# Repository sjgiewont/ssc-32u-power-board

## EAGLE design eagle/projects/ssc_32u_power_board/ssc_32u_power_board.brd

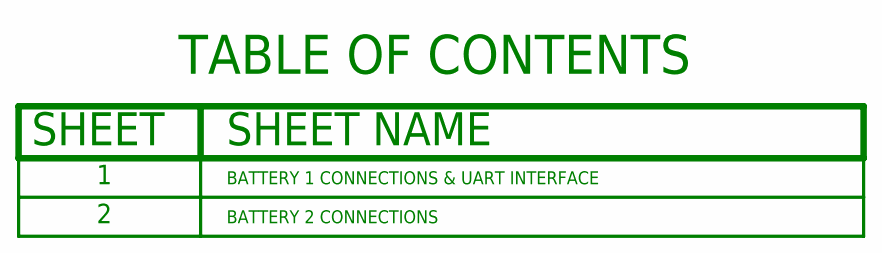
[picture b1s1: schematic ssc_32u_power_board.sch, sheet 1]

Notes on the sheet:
BATTERY 1 CONNECTIONS & UART INTERFACE
BATTERY 2 CONNECTIONS

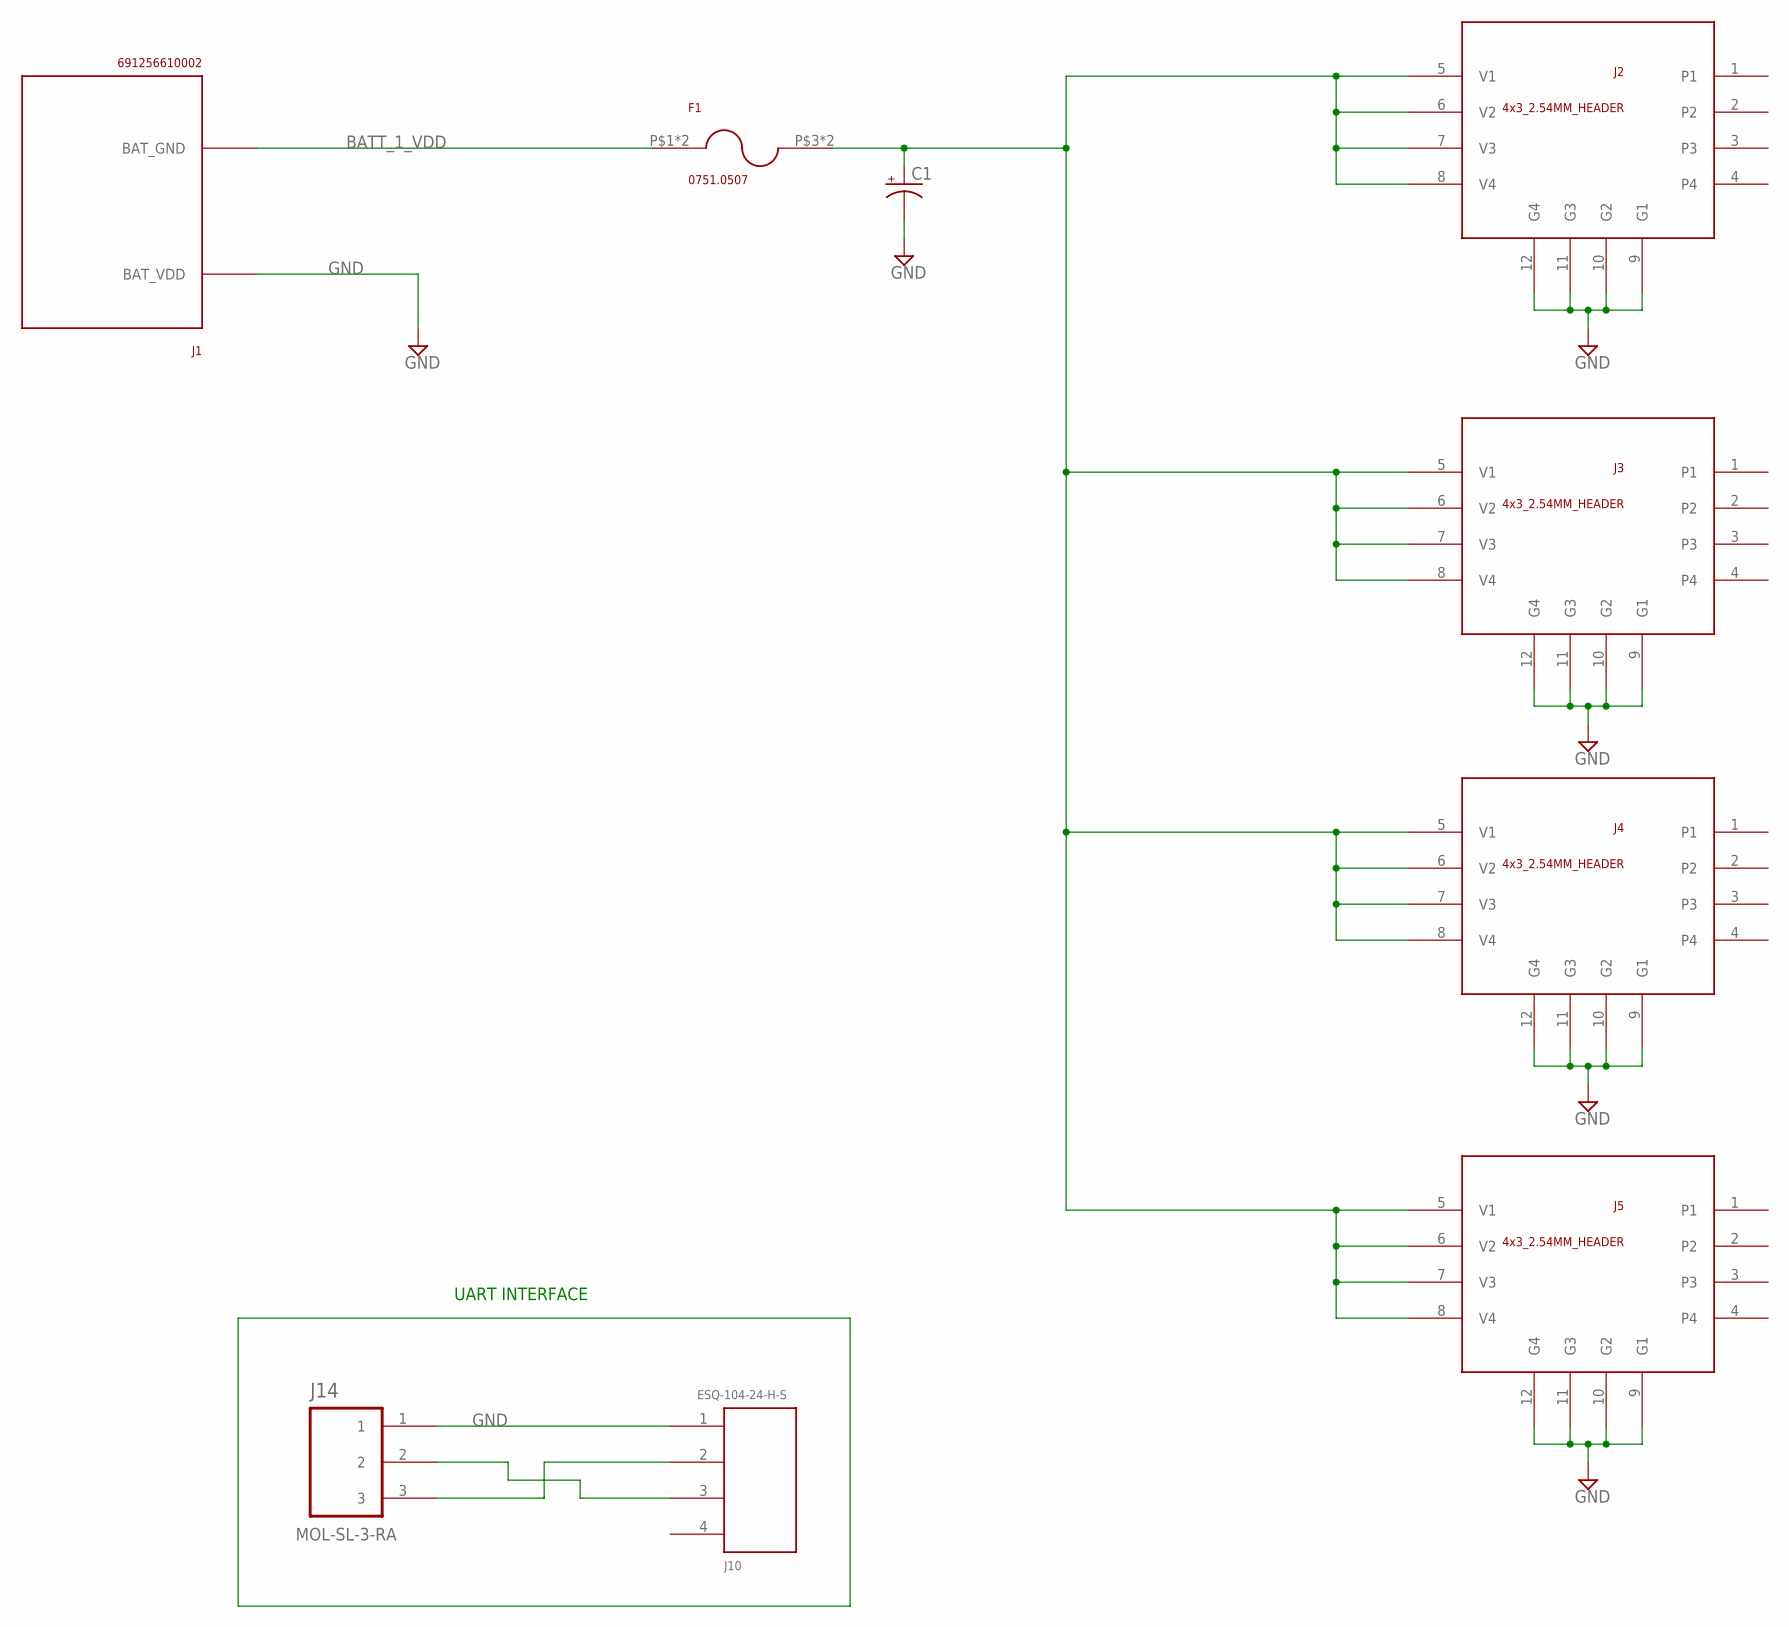
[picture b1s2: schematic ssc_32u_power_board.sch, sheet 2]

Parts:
C1: CPOL-USE5-13; E5-13
F1: 0751.0507
J1: 691256610002
J2, J3, J4, J5: 4x3_2.54MM_HEADER; 2X_ESQ-104-24-H-S__HMTSW-104-08-G-S-380
J10: ESQ-104-24-H-S
J14: MOL-SL-3-RA; MOLSL-3-RA

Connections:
BATT_1_VDD: F1.P$1, F1.P$2, J1.P$1 (BAT_GND), J1.P$2 (BAT_GND)
BBB_TX_SSC_RX: J10.2, J14.3
BBB_TX_SSC_TX: J10.3, J14.2
GND: C1.-, J1.P$3 (BAT_VDD), J1.P$4 (BAT_VDD), J2.9 (G1), J2.10 (G2), J2.11 (G3), J2.12 (G4), J3.9 (G1), J3.10 (G2), J3.11 (G3), J3.12 (G4), J4.9 (G1), J4.10 (G2), J4.11 (G3), J4.12 (G4), J5.9 (G1), J5.10 (G2), J5.11 (G3), J5.12 (G4), J10.1, J14.1; also elsewhere on the board
VBAT_1_FUSE_0_15: C1.+, F1.P$3, F1.P$4, J2.5 (V1), J2.6 (V2), J2.7 (V3), J2.8 (V4), J3.5 (V1), J3.6 (V2), J3.7 (V3), J3.8 (V4), J4.5 (V1), J4.6 (V2), J4.7 (V3), J4.8 (V4), J5.5 (V1), J5.6 (V2), J5.7 (V3), J5.8 (V4)

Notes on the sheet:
UART INTERFACE

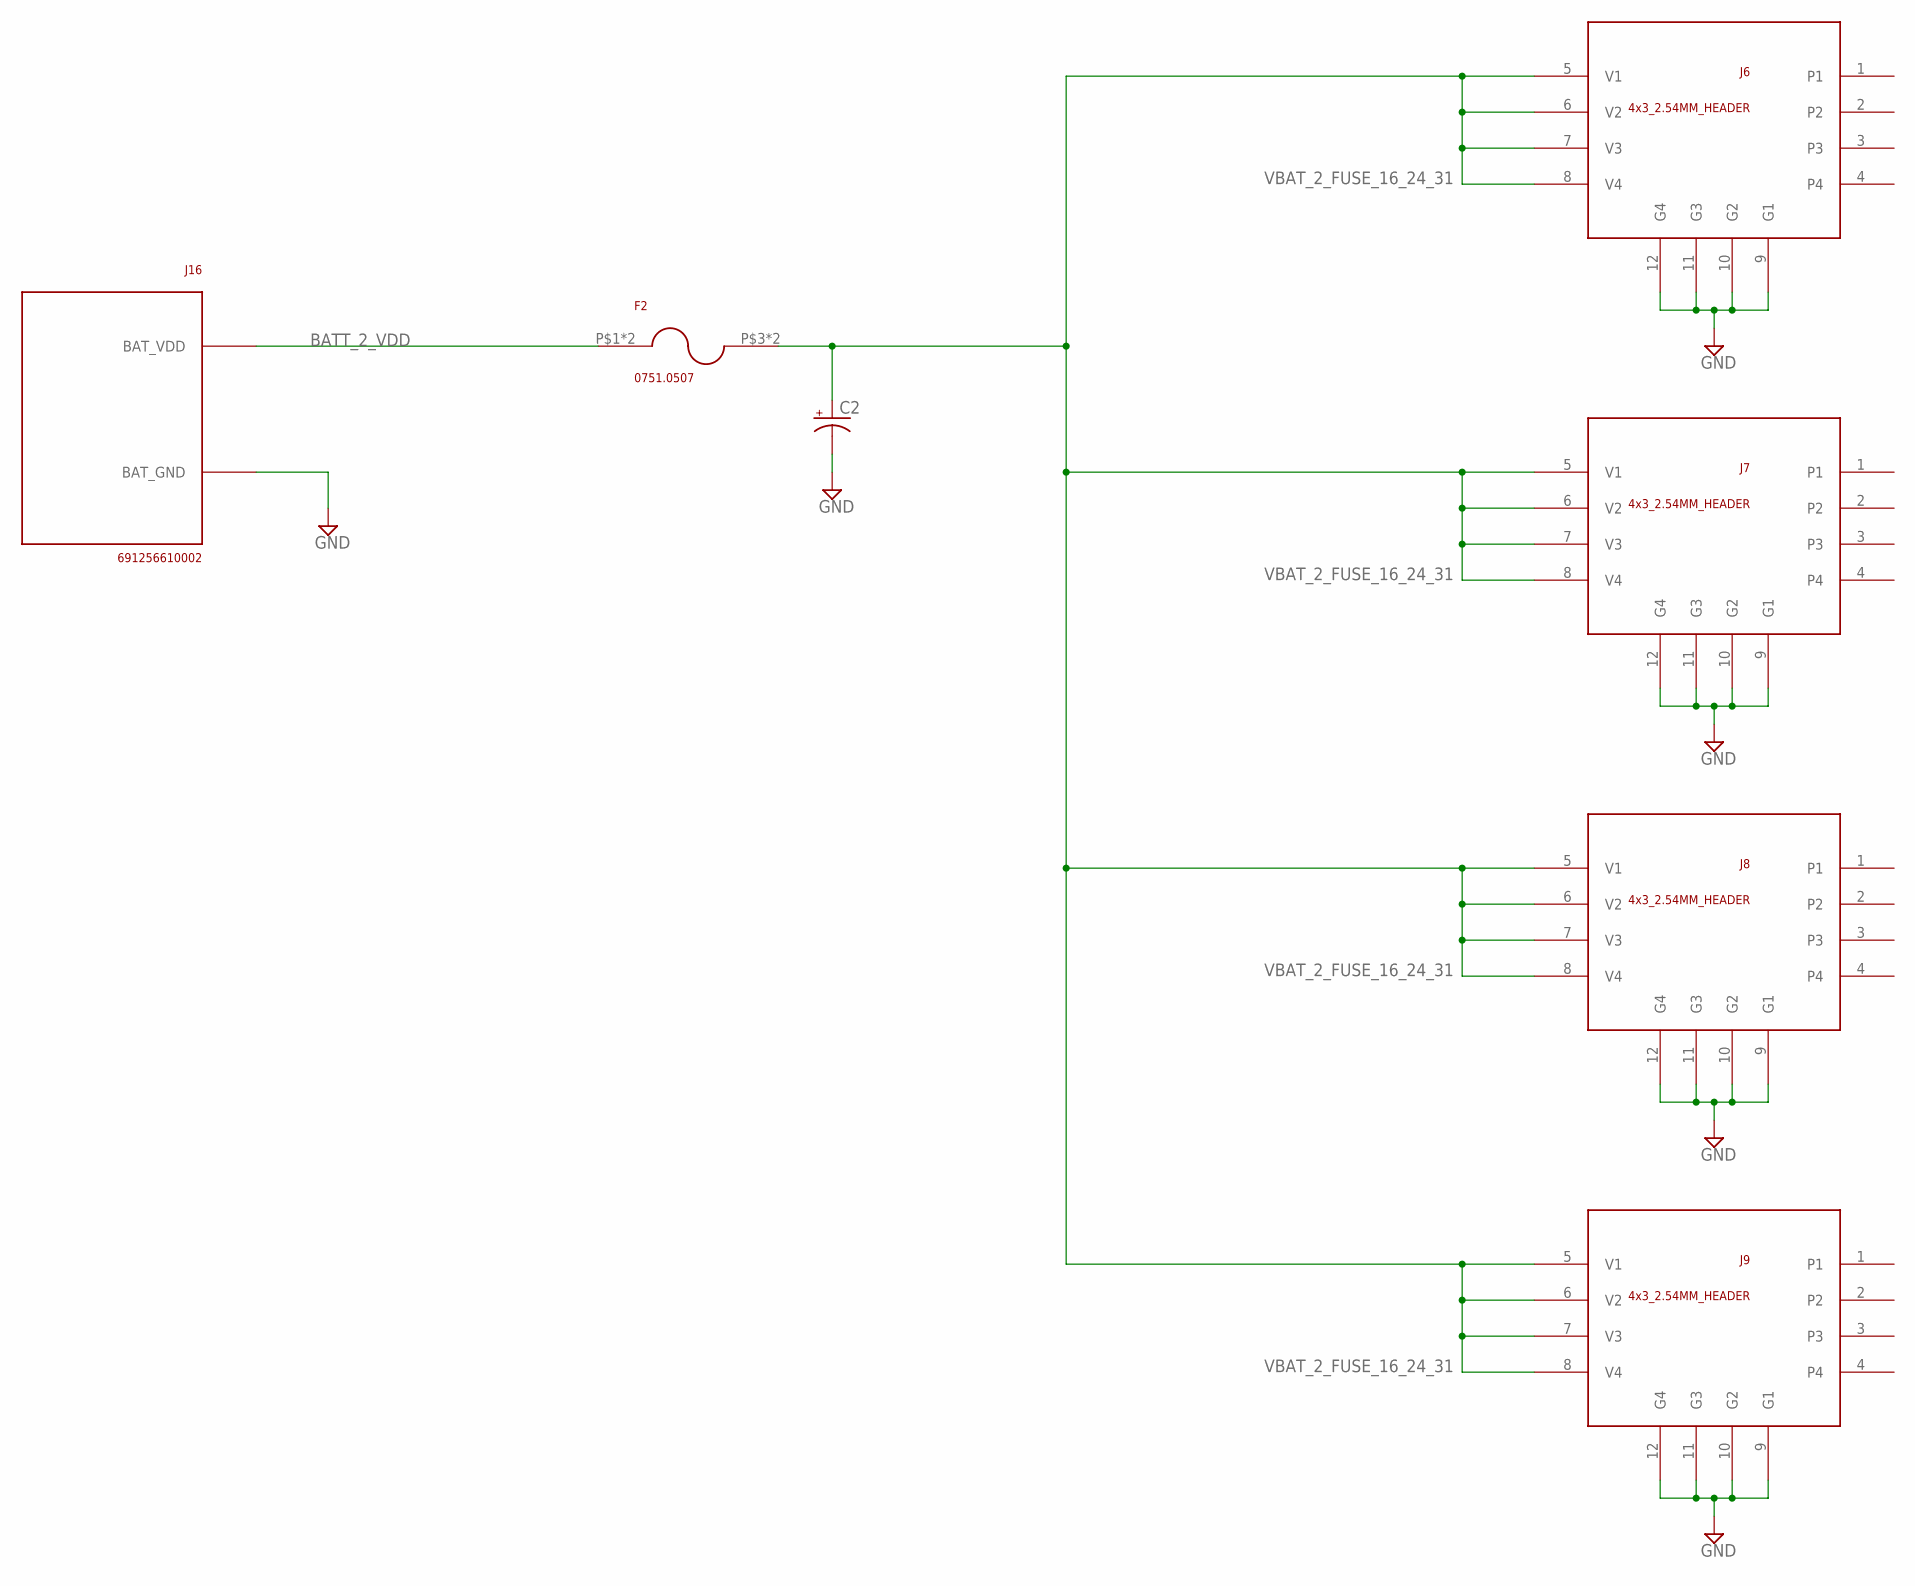
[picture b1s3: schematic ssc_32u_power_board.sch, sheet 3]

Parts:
C2: CPOL-USE5-13; E5-13
F2: 0751.0507
J6, J7, J8, J9: 4x3_2.54MM_HEADER; 2X_ESQ-104-24-H-S__HMTSW-104-08-G-S-380
J16: 691256610002

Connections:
BATT_2_VDD: F2.P$1, F2.P$2, J16.P$3 (BAT_VDD), J16.P$4 (BAT_VDD)
GND: C2.-, J6.9 (G1), J6.10 (G2), J6.11 (G3), J6.12 (G4), J7.9 (G1), J7.10 (G2), J7.11 (G3), J7.12 (G4), J8.9 (G1), J8.10 (G2), J8.11 (G3), J8.12 (G4), J9.9 (G1), J9.10 (G2), J9.11 (G3), J9.12 (G4), J16.P$1 (BAT_GND), J16.P$2 (BAT_GND); also elsewhere on the board
VBAT_2_FUSE_16_24_31: C2.+, F2.P$3, F2.P$4, J6.5 (V1), J6.6 (V2), J6.7 (V3), J6.8 (V4), J7.5 (V1), J7.6 (V2), J7.7 (V3), J7.8 (V4), J8.5 (V1), J8.6 (V2), J8.7 (V3), J8.8 (V4), J9.5 (V1), J9.6 (V2), J9.7 (V3), J9.8 (V4)

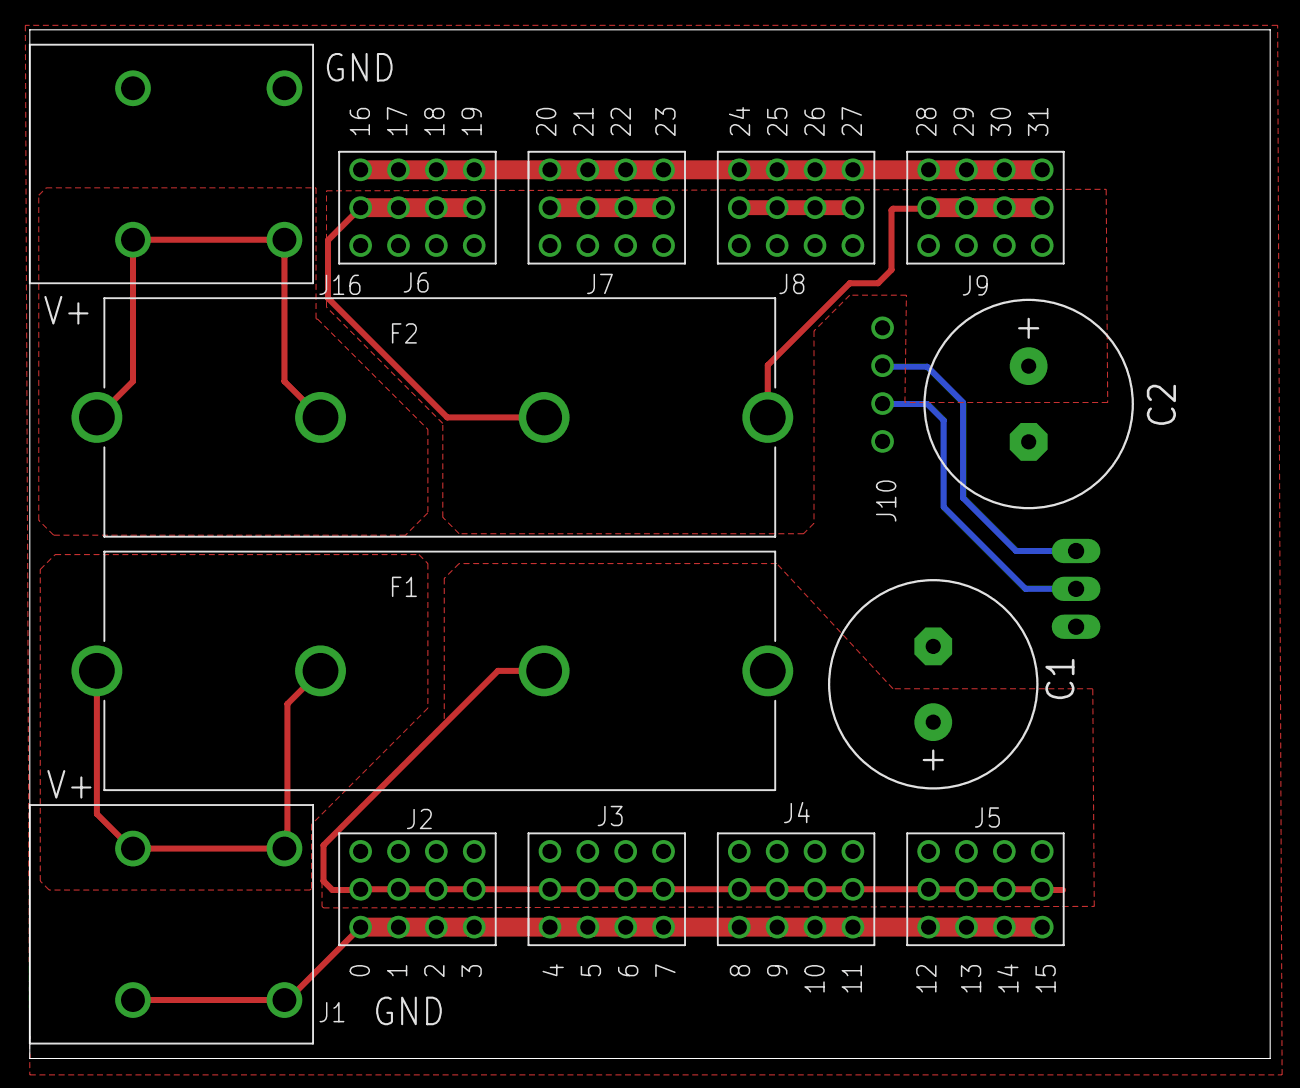
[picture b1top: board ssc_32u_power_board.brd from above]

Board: 4 copper layers, 83.2 x 69.0 mm, 16 parts (1 on the bottom side), 7 nets.

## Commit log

2017-03-24 Added Samtec connectors to library and molex 3Pin connector, started schematic with frame
2017-03-24 Finshed added all components, started board layout
2017-03-24 Finished board layout, used polygons to fill all high current traces
2017-03-28 Major modifications, removed switches and swapped out surface mount fuses for glass ones. Still two layer board
2017-03-29 Updated the silkscreen
2017-03-30 Added caps
2017-03-31 Back to one board per panel
2017-04-01 Added a pdf of the gerbers
